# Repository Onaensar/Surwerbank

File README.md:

# Surwerbank
# Hybrid Powerbank: Solar + MagSafe + 18W Fast Charge 

Welcome to the **Hybrid Survivor Powerbank** repository! This project is a fully open-source, high-efficiency power management board designed for ultimate portability and outdoor resilience. 

Unlike standard powerbanks, this board integrates **18W Bidirectional Fast Charging**, **MPPT Solar Energy Harvesting**, and **MagSafe Compatible Wireless Charging** into a single, compact PCB.

**Designed by:** Abdullah Ensar 
**Institution:** İzmir Bakırçay University, Electrical and Electronics Engineering

---

## ✨ Key Features & Core ICs

### 1. ⚡ 18W Fast Charging & Power Management (IP5328P)
At the heart of the board is the **IP5328P** SoC, handling high-efficiency bi-directional charging. 
* Supports multiple fast-charge protocols (QC3.0, PD, AFC, FCP).
* Stable 5A output capability for demanding devices.
* Deeply filtered power delivery with strategic capacitor placement (low ripple).

### 2. ☀️ MPPT Solar Harvesting (CN3791)
Built for off-grid scenarios, the board includes a dedicated **CN3791** Maximum Power Point Tracking (MPPT) circuit.
* Connect a compatible solar panel to the terminal block.
* Extracts maximum available power from the sun to trickle-charge the lithium cells, significantly extending standby and active use time in outdoor environments.

### 3. 🧲 Wireless & MagSafe Charging (IP6808)
No cables? No problem. The **IP6808** wireless charging transmitter ensures your devices stay powered up seamlessly.
* Optimized resonance capacitor array for stable Tx transmission.
* Designed to be highly compatible with MagSafe form factors.

### 4. 🛡️ Rugged & Enclosure-Ready Mechanical Design
This PCB isn't just an electrical prototype; it is designed for real-world mechanical integration.
* **Mounting Holes:** M3 mounting holes placed at the corners for secure installation inside 3D printed or waterproof enclosures.
* **Optimized Clearances:** Type-C receptacle (J2) is perfectly aligned with the board edge (Edge.Cuts) to ensure flush mounting and cable compatibility.
* *Note: The mechanical STEP file is included for easy integration into Fusion 360 / SolidWorks to design custom rugged cases.*

---

## 🛠️ Fabrication & Assembly (Gerber Files)
The board has passed all DRC checks with 0 Errors and 0 Warnings in KiCad. 
* **Layer Count:** 2 Layers
* **Copper Weight:** 1 oz (recommended) or 2 oz for enhanced thermal dissipation under 5A loads.
* **Polygons:** Generous Top and Bottom GND pours with extensive via stitching for thermal relief and low impedance.

You can find the production-ready `.zip` file containing all Gerber and Drill files in the `Fabrication` folder.

## 📄 License
This project is released under the **Open Source Hardware (OSHW)** license. Feel free to use, modify, and build upon this design!

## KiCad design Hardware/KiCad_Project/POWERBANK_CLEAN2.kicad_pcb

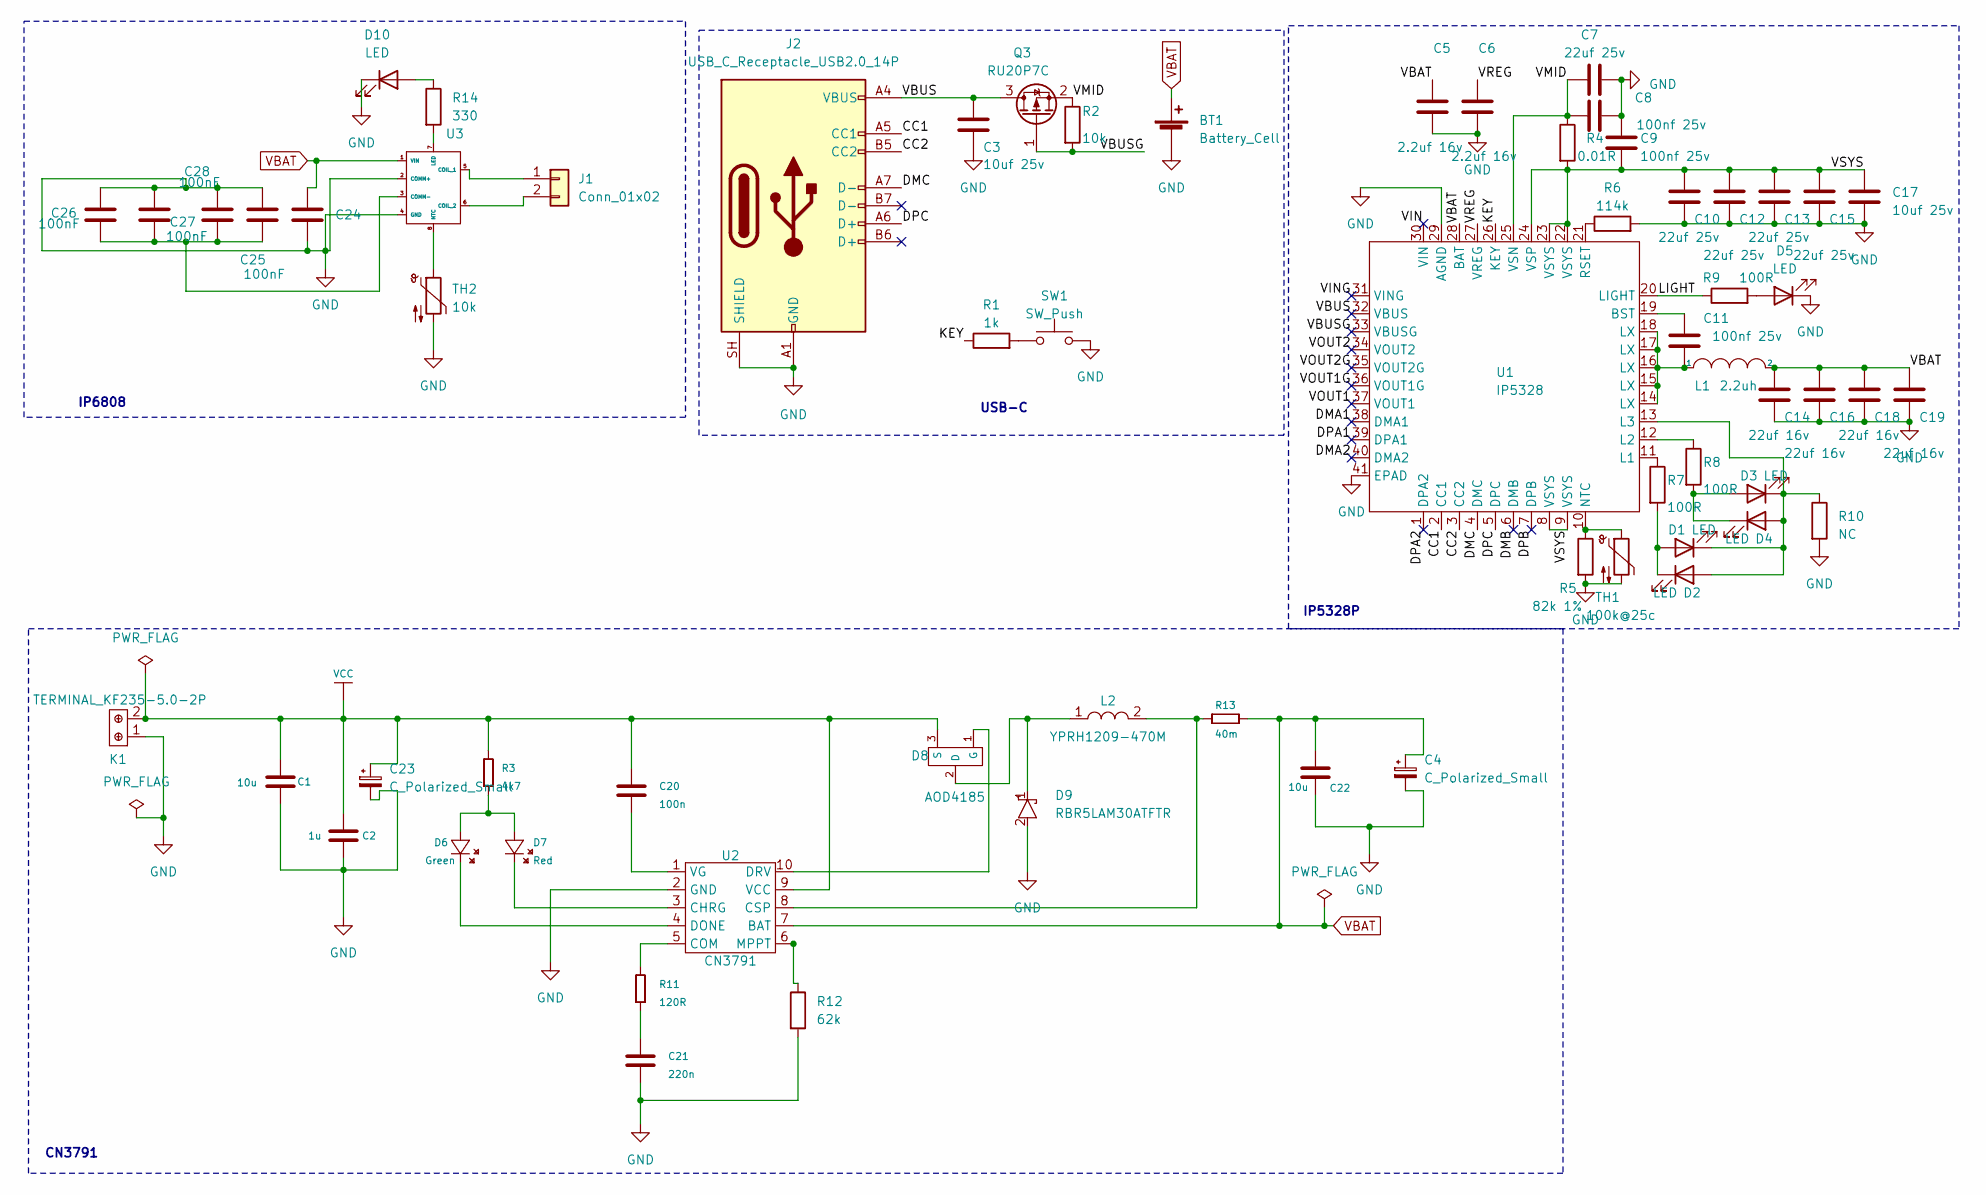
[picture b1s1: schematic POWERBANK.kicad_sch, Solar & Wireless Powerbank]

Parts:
BT1: Battery_Cell; TerminalBlock_Phoenix_MKDS-1,5-2-5.08_1x02_P5.08mm_Horizont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
C1, C22: 10u; C_0805_2012Metric
C2: 1u; C_0805_2012Metric
C3, C17: 10uf 25v; C_1206_3216Metric
C4, C23: C_Polarized_Small; CP_Elec_4x5.7
C5, C6: 2.2uf 16v; C_0805_2012Metric
C7, C15: 22uf 25v; C_1206_3216Metric
C8, C9, C11: 100nf 25v; C_0603_1608Metric
C10, C12, C13: 22uf 25v; C_0805_2012Metric
C14, C16, C18, C19: 22uf 16v; C_1206_3216Metric
C20: 100n; C_0805_2012Metric
C21: 220n; C_0805_2012Metric
C24: 10uF; C_0805_2012Metric
C25, C26, C27, C28: 100nF; C_0805_2012Metric
D1, D2, D3, D4, D5: LED; LED_0603_1608Metric
D6: Green; LED_0805_2012Metric
D7: Red; LED_0805_2012Metric
D8: AOD4185; TO-252-2
D9: RBR5LAM30ATFTR; D_SMB
D10: LED; LED_0805_2012Metric
J1: Conn_01x02; PinHeader_1x02_P2.54mm_Vertical
J2: USB_C_Receptacle_USB2.0_14P; USB_C_Receptacle_HRO_TYPE-C-31-M-12
K1: TERMINAL_KF235-5.0-2P; TerminalBlock_Phoenix_MKDS-1,5-2-5.08_1x02_P5.08mm_Horizont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
L1: 2.2uh; L_12x12mm_H4.5mm
L2: YPRH1209-470M; L_12x12mm_H4.5mm
Q3: RU20P7C; SOT-23
R1: 1k; R_0603_1608Metric
R2: 10k; R_0603_1608Metric
R3: 4k7; R_0805_2012Metric
R4: 0.01R; R_1206_3216Metric
R5: 82k 1%; R_0603_1608Metric
R6: 114k; R_0603_1608Metric
R7, R8, R9: 100R; R_0603_1608Metric
R10: NC; R_0603_1608Metric
R11: 120R; R_0805_2012Metric
R12: 62k; R_0805_2012Metric
R13: 40m; R_0805_2012Metric
R14: 330; R_0805_2012Metric
SW1: SW_Push; SW_Push_1P1T_NO_CK_KMR2
TH1: 100k@25c; R_0805_2012Metric
TH2: 10k; PinHeader_1x02_P2.54mm_Vertical
U1: IP5328; QFN-40-1EP_6x6mm_P0.5mm_EP4.6x4.6mm
U2: CN3791; SSOP-10_3.9x4.9mm_P1.00mm
U3: SOIC-8_3.9x4.9mm_P1.27mm

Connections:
/CC1: J2.A5 (CC1), U1.2 (CC1)
/CC2: J2.B5 (CC2), U1.3 (CC2)
/DMA1: U1.38 (DMA1)
/DMA2: U1.40 (DMA2)
/DMB: U1.6 (DMB)
/DMC: J2.A7 (D-), U1.4 (DMC)
/DPA1: U1.39 (DPA1)
/DPA2: U1.1 (DPA2)
/DPB: U1.7 (DPB)
/DPC: J2.A6 (D+), U1.5 (DPC)
/KEY: R1.1, U1.26 (KEY)
/LIGHT: R9.1, U1.20 (LIGHT)
/VBUS: C3.1, J2.A4 (VBUS), J2.A9 (VBUS), J2.B4 (VBUS), J2.B9 (VBUS), Q3.3 (D), U1.32 (VBUS)
/VBUSG: Q3.1 (G), R2.2, U1.33 (VBUSG)
/VIN: U1.30 (VIN)
/VING: U1.31 (VING)
/VMID: C7.1, C8.1, Q3.2 (S), R2.1, R4.1, U1.25 (VSN)
/VOUT1: U1.37 (VOUT1)
/VOUT1G: U1.36 (VOUT1G)
/VOUT2: U1.34 (VOUT2)
/VOUT2G: U1.35 (VOUT2G)
/VREG: C6.1, U1.27 (VREG)
/VSYS: C9.2, C10.1, C12.1, C13.1, C15.1, C17.1, R4.2, U1.8 (VSYS), U1.9 (VSYS), U1.22 (VSYS), U1.23 (VSYS), U1.24 (VSP)
GND: BT1.2 (-), C1.1, C2.1, C3.2, C4.2, C5.2, C6.2, C7.2, C8.2, C9.1, C10.2, C12.2, C13.2, C14.2, C15.2, C16.2, C17.2, C18.2, C19.2, C21.1, C22.1, C23.2, C24.2, C25.1, C26.1, C27.1, C28.1, D5.1 (K), D9.2 (A), D10.1 (K), J2.A1 (GND), J2.A12 (GND), J2.B1 (GND), J2.B12 (GND), J2.SH (SHIELD), K1.1, R5.2, R6.2, R10.2, R12.2, SW1.2, TH1.2, TH2.2, U1.29 (AGND), U1.41 (EPAD), U2.2 (GND), U3.2 (COMM+), U3.4 (GND)
unnamed: C11.2, L1.1, U1.14 (LX), U1.15 (LX), U1.16 (LX), U1.17 (LX), U1.18 (LX)
unnamed: C21.2, R11.1
unnamed: D1.2 (A), D2.1 (K), R7.2
unnamed: D1.1 (K), D2.2 (A), D3.1 (K), D4.2 (A), R10.1, U1.13 (L3)
unnamed: D3.2 (A), D4.1 (K), R8.2
unnamed: D5.2 (A), R9.2
unnamed: D6.1 (A), D7.1 (A), R3.1
unnamed: D6.2 (K), U2.4 (DONE)
unnamed: D7.2 (K), U2.3 (CHRG)
unnamed: D8.2 (D), D9.1 (C), L2.1
unnamed: D8.1 (G), U2.10 (DRV)
unnamed: D10.2 (A), R14.1
unnamed: J1.1, U3.5 (COIL_1)
unnamed: J1.2, U3.6 (COIL_2)
unnamed: R1.2, SW1.1
unnamed: C11.1, U1.19 (BST)
unnamed: R7.1, U1.11 (L1)
unnamed: R8.1, U1.12 (L2)
unnamed: R5.1, TH1.1, U1.10 (NTC)
unnamed: R6.1, U1.21 (RSET)
unnamed: R11.2, U2.5 (COM)
unnamed: L2.2, R13.1, U2.8 (CSP)
unnamed: R12.1, U2.6 (MPPT)
unnamed: C20.1, U2.1 (VG)
unnamed: C25.2, C26.2, C27.2, C28.2, U3.3 (COMM-)
unnamed: R14.2, U3.7 (LED)
unnamed: TH2.1, U3.8 (NTC)
VBAT: BT1.1 (+), C4.1, C5.1, C14.1, C16.1, C18.1, C19.1, C22.2, C24.1, L1.2, R13.2, U1.28 (BAT), U2.7 (BAT), U3.1 (VIN)
VCC: C1.2, C2.2, C20.2, C23.1, D8.3 (S), K1.2, R3.2, U2.9 (VCC)

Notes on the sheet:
IP5328P
CN3791
USB-C
IP6808

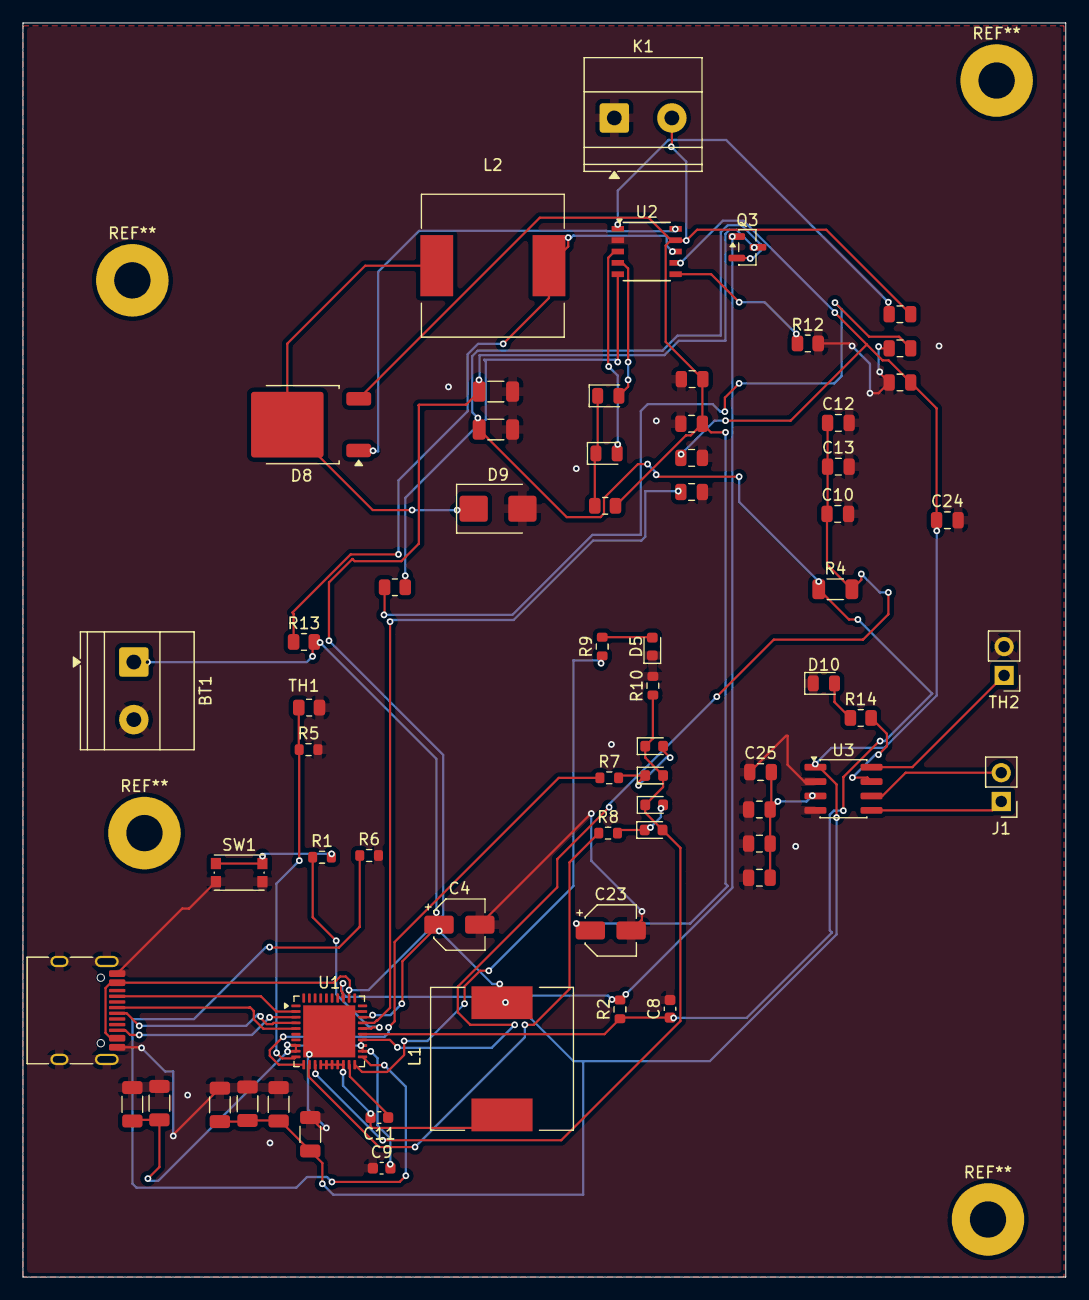
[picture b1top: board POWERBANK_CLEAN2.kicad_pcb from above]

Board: 2 copper layers, 92.0 x 110.6 mm, 65 parts (0 on the bottom side), 41 nets.

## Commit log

2026-06-25 README.md
